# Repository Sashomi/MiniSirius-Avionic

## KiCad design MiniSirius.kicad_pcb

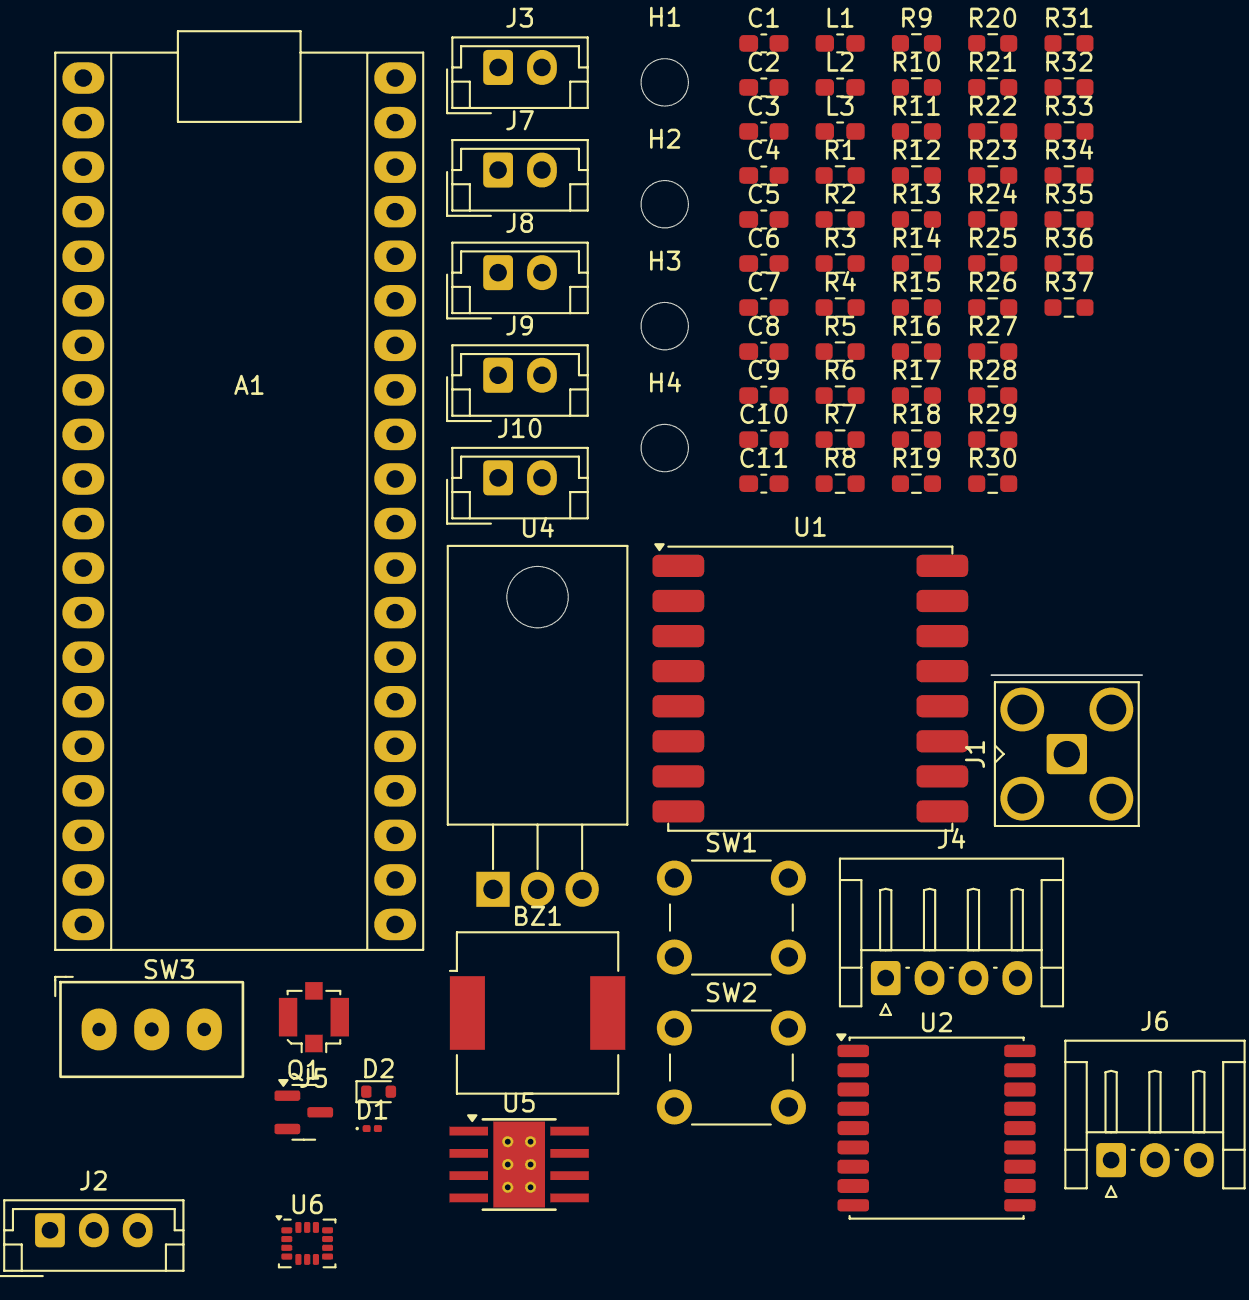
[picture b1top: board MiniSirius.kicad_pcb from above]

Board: 2 copper layers, 78 parts (0 on the bottom side), 64 nets, no tracks yet.

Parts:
A1: Raspberry_Pi_Pico_THT; raspberry_pi_pico_THT
BZ1: Buzzer; Buzzer_CUI_CPT-9019S-SMT
C1, C2, C3, C4, C5: NC; C_0603_1608Metric_Pad1.08x0.95mm_HandSolder
C6, C7, C10, C11: 100nF; C_0603_1608Metric_Pad1.08x0.95mm_HandSolder
C8, C9: 0.1µF; C_0603_1608Metric_Pad1.08x0.95mm_HandSolder
D1: LED; LED_0201_0603Metric
D2: 1N4148WT; D_SOD-523
H1, H2, H3, H4: MountingHole; MountingHole_2.7mm_M2.5
J1: Conn_Coaxial_SMA; SMA_Amphenol_901-143_Horizontal
J2: JST_03; JST_EH_B3B-EH-A_1x03_P2.50mm_Vertical
J3, J7, J8, J9, J10: JST_02; JST_EH_B2B-EH-A_1x02_P2.50mm_Vertical
J4: JST_04; JST_EH_S4B-EH_1x04_P2.50mm_Horizontal
J5: Molex_MCRF_73412-0110; U.FL_Molex_MCRF_73412-0110_Vertical
J6: JST_03; JST_EH_S3B-EH_1x03_P2.50mm_Horizontal
L1, L2, L3: NC; L_0603_1608Metric_Pad1.05x0.95mm_HandSolder
Q1: BSS138; SOT-23
R1, R4, R5, R6, R7, R8, R9, R10, R11, R12, R13, R14, R15, R16, R17, R18, R20, R21, R22, R23, R24, R25, R29, R30: 0R; R_0603_1608Metric_Pad0.98x0.95mm_HandSolder
R2, R19, R32, R34, R35, R36, R37: 10k; R_0603_1608Metric_Pad0.98x0.95mm_HandSolder
R3: 260R; R_0603_1608Metric_Pad0.98x0.95mm_HandSolder
R26: NC; R_0603_1608Metric_Pad0.98x0.95mm_HandSolder
R27, R28: 4.7k; R_0603_1608Metric_Pad0.98x0.95mm_HandSolder
R31: 0.2R; R_0603_1608Metric_Pad0.98x0.95mm_HandSolder
R33: 5.1k; R_0603_1608Metric_Pad0.98x0.95mm_HandSolder
SW1, SW2: Push_Button; SW_PUSH_6mm
SW3: Slide_Switch_SPDT; Slide_Switch_SPDT_P3mm_10x5x10mm
U1: RFM95W-868S2; HOPERF_RFM9XW_SMD
U2: MAX-M10S; ublox_MAX
U4: L7805; TO-220-3_Horizontal_TabDown
U5: DRV8870DDA; Texas_HTSOP-8-1EP_3.9x4.9mm_P1.27mm_EP2.95x4.9mm_Mask2.4x3.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
U6: LSM6DSL; LGA-14_3x2.5mm_P0.5mm_LayoutBorder3x4y

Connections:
+3V3: A1.3 (GND), A1.8 (GND), A1.13 (GND), A1.18 (GND), A1.23 (GND), A1.28 (GND), A1.33 (GND), A1.36 (3V3(OUT)), A1.38 (GND), C1.2, C2.2, C3.2, C4.2, C5.2, C6.2, C7.2, C8.2, C9.2, C10.1, C10.2, C11.1, C11.2, D1.1 (K), J1.2 (Ext), J2.2, J2.3, J4.3, J4.4, J5.2 (Ext), J6.1, J7.2, J8.2, J9.1, J10.1, Q1.2 (S), R2.2, R17.1, R18.1, R19.2, R27.1, R28.1, R31.2, R32.1, R34.2, R35.1, R36.1, R37.1, SW1.2, SW2.2, U1.1 (GND), U1.8 (GND), U1.10 (GND), U1.13 (3.3V), U2.1 (GND), U2.10 (GND), U2.12 (GND), U4.2 (GND), U5.1 (GND), U5.4 (VREF), U5.9 (GND), U6.1 (SDO/SA0), U6.2 (SDX), U6.3 (SCX), U6.5 (VDDIO), U6.6 (GND), U6.7 (GND), U6.8 (VDD), U6.12 (CS)
+5V: A1.39 (VSYS), C7.1, U4.3 (OUT)
/ACCELERO: A1.5 (GP3), J3.1
/BUZZER_PIN: Q1.1 (G), R32.2
/GPS_RF_IN: L2.2, R29.1, U2.11 (RF_IN)
/INT1_IMU: A1.1 (GP0), U6.4 (INT1)
/INT2_IMU: A1.2 (GP1), U6.9 (INT2)
/JACK: A1.20 (GP15), J10.2, R37.2
/LORA_RF_OUT: R1.1, U1.9 (ANT)
/M1: A1.27 (GP21), U5.3 (IN1)
/M1_Button: A1.9 (GP6), R2.1, SW1.1
/M2: A1.26 (GP20), U5.2 (IN2)
/M2_Button: A1.10 (GP7), R19.1, SW2.1
/PPS: R3.1, U2.4 (TIMEPULSE)
/RBF: A1.34 (ADC2/GP28), J9.2, R36.2
/TODO: J3.2, R35.2
/VBAT: BZ1.1 (+), C8.1, C9.1, D2.1 (K), R33.2, R34.1, U5.5 (VM)
/VCC_RF: R26.1, U2.14 (VCC_RF)
DIO0_RF: A1.7 (GP5), R25.2
DIO1_RF: A1.6 (GP4), R24.2
EXTINT: A1.31 (ADC0/GP26), R9.1
MISO_RF: A1.16 (GP12), R6.1
MOSI_RF: A1.15 (GP11), R5.1
unnamed: BZ1.2 (-), D2.2 (A), Q1.3 (D)
unnamed: C1.1, L1.1, R1.2, R16.1
unnamed: C3.1, L2.1, R26.2
unnamed: C4.1, L3.1, R29.2, R30.1
unnamed: D1.2 (A), R3.2
unnamed: C2.1, J1.1 (In), L1.2, R16.2
unnamed: C5.1, J5.1 (In), L3.2, R30.2
unnamed: J6.3, SW3.1
unnamed: R25.1, U1.14 (DIO0)
unnamed: R24.1, U1.15 (DIO1)
unnamed: R23.1, U1.16 (DIO2)
unnamed: R22.1, U1.11 (DIO3)
unnamed: R21.1, U1.12 (DIO4)
unnamed: R20.1, U1.7 (DIO5)
unnamed: R6.2, U1.2 (MISO)
unnamed: R5.2, U1.3 (MOSI)
unnamed: R7.2, U1.5 (NSS)
unnamed: R8.2, U1.6 (RESET)
unnamed: R4.2, U1.4 (SCK)
unnamed: R9.2, U2.5 (EXTINT)
unnamed: R12.2, U2.3 (RXD)
unnamed: R15.2, U2.17 (SCL)
unnamed: R14.2, U2.16 (SDA)
unnamed: R13.2, U2.2 (TXD)
unnamed: R17.2, U2.8 (VCC)
unnamed: R18.2, U2.7 (VCC_IO)
unnamed: R11.2, U2.9 (~RESET)
unnamed: R10.2, U2.18 (~SAFEBOOT)
unnamed: C6.1, R33.1, SW3.3, U4.1 (IN)
unnamed: R31.1, U5.7 (ISEN)
unnamed: J7.1, U5.6 (OUT1)
unnamed: J8.1, U5.8 (OUT2)
RESET_GPS: A1.25 (GP19), R11.1
RST_RF: A1.19 (GP14), R8.1
RX_GPS: A1.12 (GP9), R12.1
SAFE_GPS: A1.32 (ADC1/GP27), R10.1
SCK_RF: A1.14 (GP10), R4.1
SCL: A1.22 (GP17), J4.2, R15.1, R28.2, U6.13 (SCL)
SDA: A1.21 (GP16), J4.1, R14.1, R27.2, U6.14 (SDA)
SS_RF: A1.17 (GP13), R7.1
TX_GPS: A1.11 (GP8), R13.1

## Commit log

2025-07-20 update schematic
2025-07-23 Update Schematic with buzzer, IMU and motor control + schematic pdf export
